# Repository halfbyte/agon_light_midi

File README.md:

# Agon Light MIDI interface and software

My goal is to enable Agon Light to be able to confidently speak MIDI from both native and BASIC code

## Current state

I'll be prototyping a simple MIDI adapter suitable for the UEXT adapter present on the Olimex version of the Agon Light. The idea here is that a MIDI adapter for UEXT would benefit more people than just Agon Light users and maybe that way I can coax Olimex into making these in the future. Adapting the hardware for the standard GPIO header on all Agon Lights should be easy, so when the hardware gets to the board design state, I am more than happy to accept contributions to make that a thing.

I haven't started on the software side yet, mainly because I don't have the hardware yet.

## Hardware design

My first version will be a bread board prototype. I have built MIDI circuits (for Arduino, for example) in the past and I have found a couple of similar designs that should work with the 3.3V design of the Agon Light.

Next step will either be a stripboard design (The parts count for this is very low) or a simple trough hole PCB design (mostly because I have all the parts as through hole components lying around)

The kicad files currently found in the repo are more or less just training data, I am quite new to kicad so bear with me.

## MIDI In Circuit

Is based on [Kevin's ](https://diyelectromusic.wordpress.com/2021/02/15/midi-in-for-3-3v-microcontrollers/) 3.3V MIDI in circuit (Version 2, based on the H11L1 optocoupler)

## MIDI Out Circuit

Is based on the official MIDI hardware addendum for 3.3V based systems.

## Licenses

Software licensed under MIT License, see [software/LICENSE](software/LICENSE)

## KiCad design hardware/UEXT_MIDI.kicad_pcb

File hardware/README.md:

# UEXT MIDI Interface

Although specifically made for my AgonLight2, this interface should work for all boards with a UEXT connector if the UART is exposed.

## Status

Prototyping phase. The kicad files in this repo are just me playing around. The schematics are almost done (I wonder if I need to include the optional buffer that, I think is not present on the UEXT header in contrast to the GPIO headers), but the layout is just a first try.

I will breadboard the in- and output circuits first before continuing with the board design.

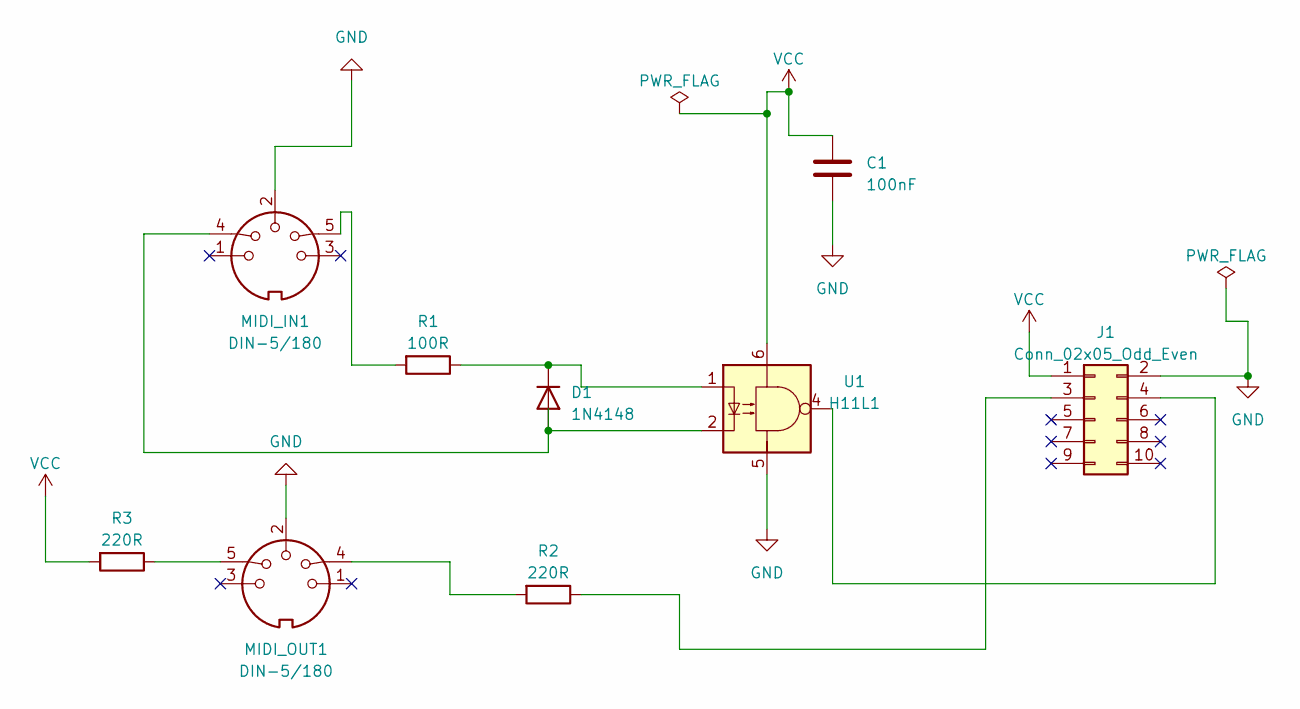
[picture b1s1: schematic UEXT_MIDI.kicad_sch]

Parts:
C1: 100nF; CP_Axial_L18.0mm_D6.5mm_P25.00mm_Horizontal
D1: 1N4148; D_DO-35_SOD27_P7.62mm_Horizontal
J1: Conn_02x05_Odd_Even; PinHeader_2x06_P2.54mm_Vertical
MIDI_IN1: DIN-5/180; MIDI_DIN5
MIDI_OUT1: DIN-5/180; MIDI_DIN5
R1: 100R; R_Axial_DIN0207_L6.3mm_D2.5mm_P5.08mm_Vertical
R2, R3: 220R; R_Axial_DIN0411_L9.9mm_D3.6mm_P15.24mm_Horizontal
U1: H11L1; DIP-6_W7.62mm

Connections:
GND: C1.2, J1.2, MIDI_IN1.2, MIDI_OUT1.2, U1.5
unnamed: D1.2 (A), MIDI_IN1.4, U1.2
unnamed: D1.1 (K), R1.1, U1.1
unnamed: J1.3, R2.1
unnamed: J1.4, U1.4
unnamed: MIDI_IN1.5, R1.2
unnamed: MIDI_OUT1.4, R2.2
unnamed: MIDI_OUT1.5, R3.1
VCC: C1.1, J1.1, R3.2, U1.6

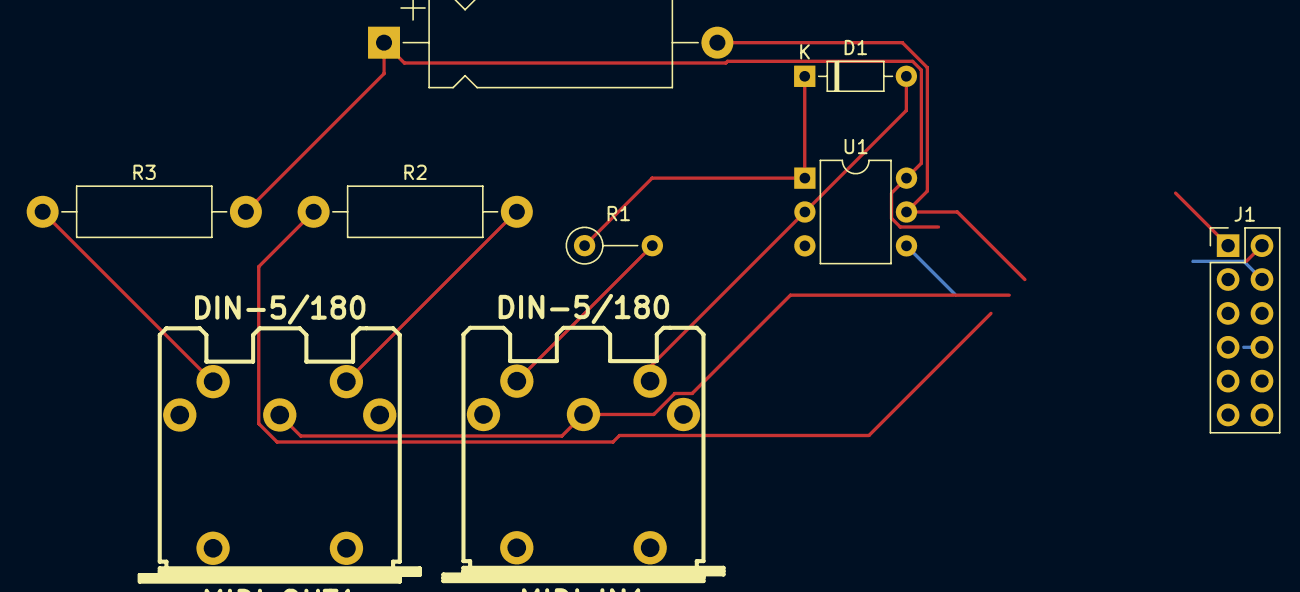
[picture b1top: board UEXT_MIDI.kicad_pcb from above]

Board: 2 copper layers, 9 parts (0 on the bottom side), 9 nets.

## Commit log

2023-06-01 Initial commit of assembler demos
